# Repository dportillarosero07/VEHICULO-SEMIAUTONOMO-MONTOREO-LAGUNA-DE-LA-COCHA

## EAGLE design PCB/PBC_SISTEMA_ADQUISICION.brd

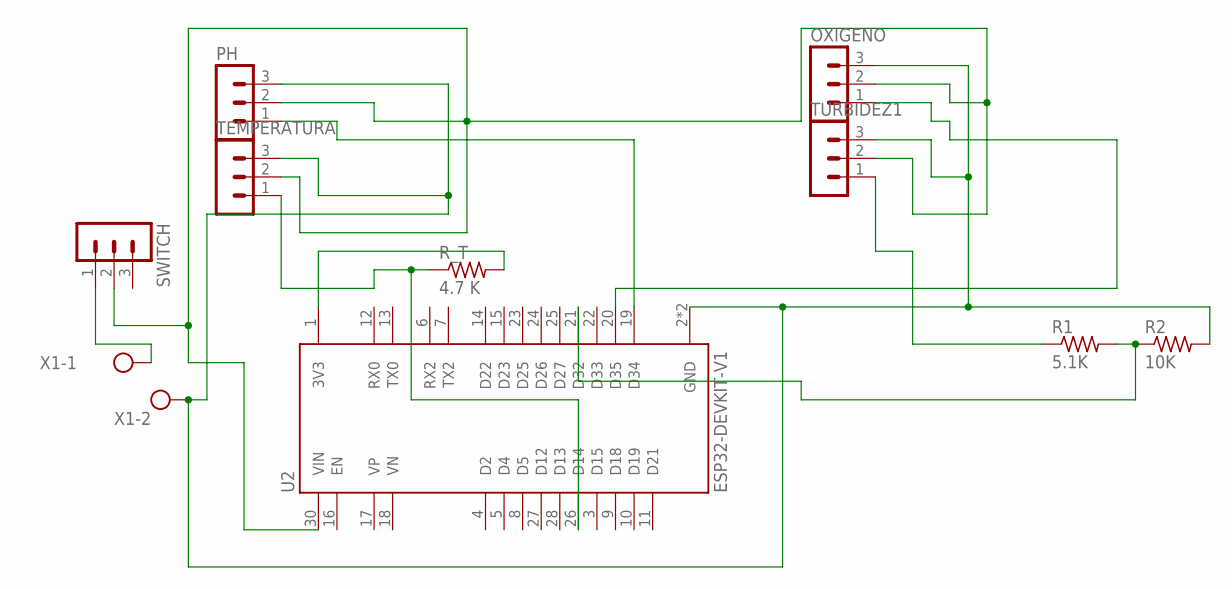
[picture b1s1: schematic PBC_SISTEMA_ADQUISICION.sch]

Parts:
OXIGENO: MA03-1
PH: MA03-1
R1: 5.1K; 0207/7
R2: 10K; 0207/7
R_T: 4.7 K; 0207/7
SWITCH: MA03-1
TEMPERATURA: MA03-1
TURBIDEZ1: MA03-1
U2: ESP32-DEVKIT-V1; MODULE_ESP32_DEVKIT_V1
X1: W237-102

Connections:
GND: OXIGENO.3, PH.3, R2.2, TEMPERATURA.3, TURBIDEZ1.3, U2.2 (GND), U2.29 (GND), X1.2
unnamed: R1.2, R2.1, U2.21 (D32)
unnamed: OXIGENO.2, PH.2, SWITCH.2, TEMPERATURA.2, TURBIDEZ1.2, U2.30 (VIN)
unnamed: OXIGENO.1, U2.20 (D35)
unnamed: R1.1, TURBIDEZ1.1
unnamed: PH.1, U2.19 (D34)
unnamed: R_T.2, U2.1 (3V3)
unnamed: R_T.1, TEMPERATURA.1, U2.26 (D14)
unnamed: SWITCH.1, X1.1

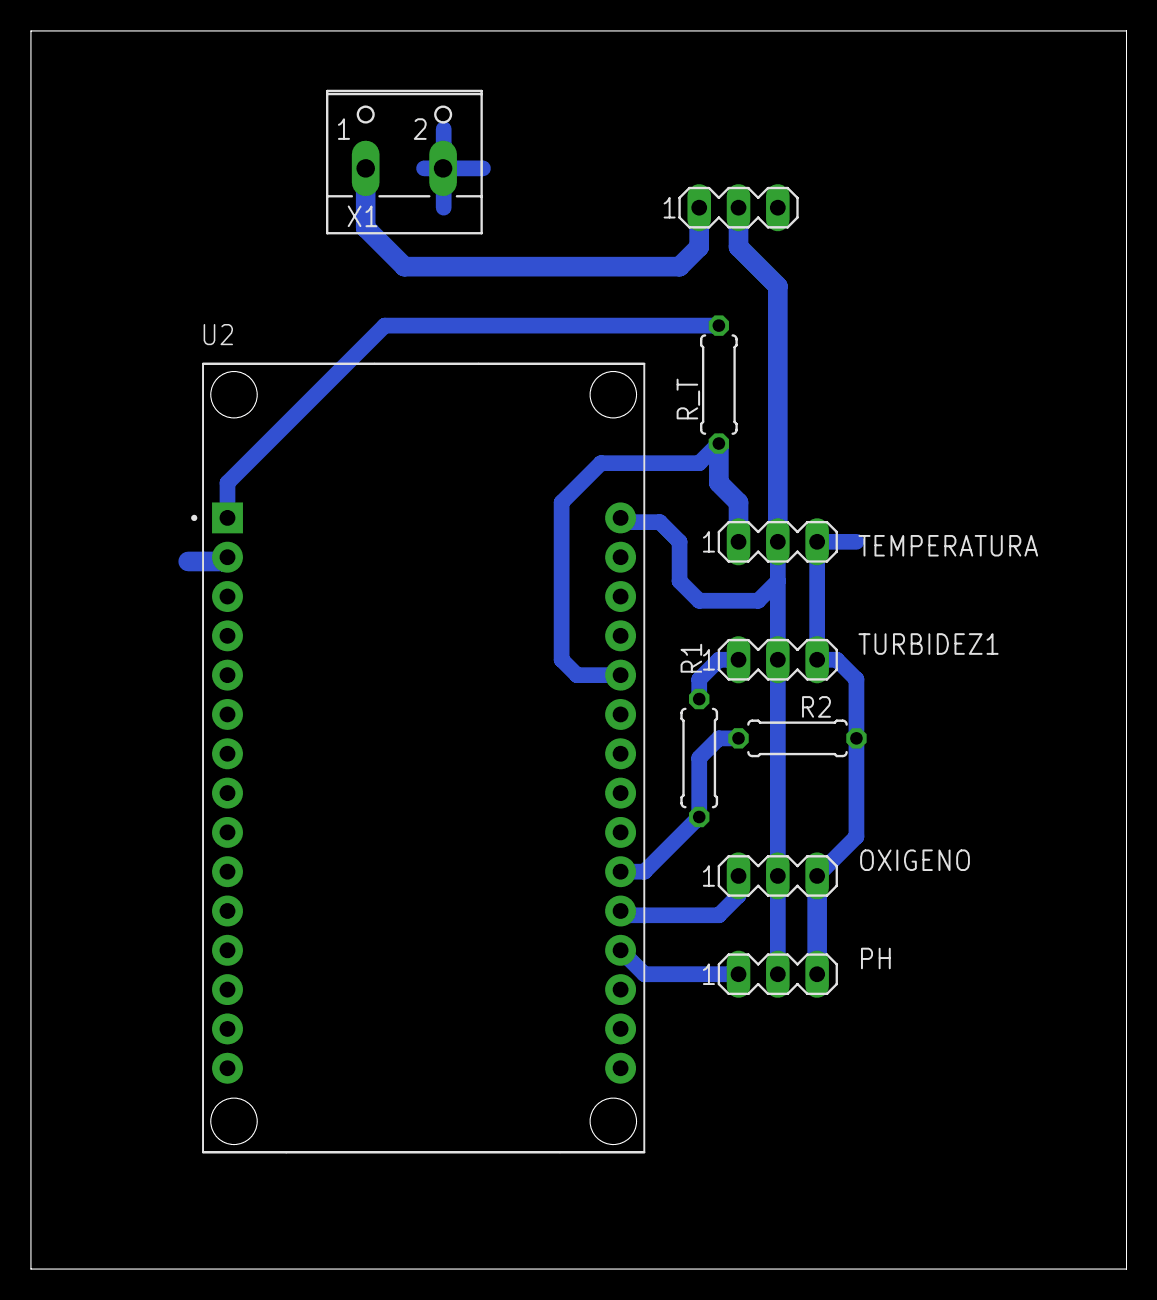
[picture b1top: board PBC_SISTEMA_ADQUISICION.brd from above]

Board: 2 copper layers, 70.8 x 80.0 mm, 10 parts (0 on the bottom side), 9 nets.
